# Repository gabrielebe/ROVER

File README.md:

# ROVER
Rover delevoped for the secondary school exam

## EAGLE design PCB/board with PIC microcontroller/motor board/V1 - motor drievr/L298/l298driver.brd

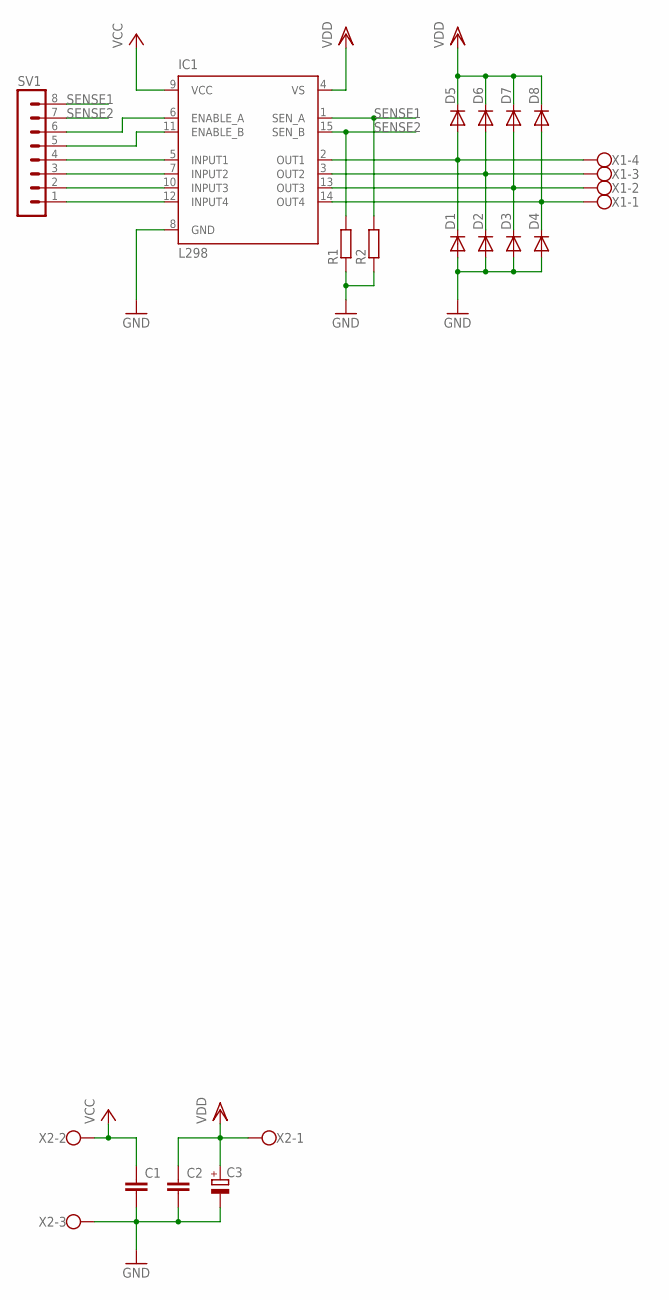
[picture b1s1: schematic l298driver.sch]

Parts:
C1, C2: C-EU050-024X044; C050-024X044
C3: CPOL-EUE3.5-10; E3,5-10
D1, D2, D3, D4, D5, D6, D7, D8: BA157; P1-10
IC1: L298; MULTIWATT-15
R1, R2: R-EU_RDH/15; RDH/15
SV1: MA08-1
X1: W237-4
X2: W237-103

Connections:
GND: C1.2, C2.2, C3.-, D1.A, D2.A, D3.A, D4.A, IC1.8 (GND), R1.1, R2.1, X2.3
unnamed: D1.C, D5.A, IC1.2 (OUT1), X1.4
unnamed: D2.C, D6.A, IC1.3 (OUT2), X1.3
unnamed: D3.C, D7.A, IC1.13 (OUT3), X1.2
unnamed: D4.C, D8.A, IC1.14 (OUT4), X1.1
unnamed: IC1.12 (INPUT4), SV1.1
unnamed: IC1.10 (INPUT3), SV1.2
unnamed: IC1.7 (INPUT2), SV1.3
unnamed: IC1.5 (INPUT1), SV1.4
unnamed: IC1.11 (ENABLE_B), SV1.5
unnamed: IC1.6 (ENABLE_A), SV1.6
SENSE1: IC1.1 (SEN_A), R2.2, SV1.8
SENSE2: IC1.15 (SEN_B), R1.2, SV1.7
VCC: C1.1, IC1.9 (VCC), X2.2
VDD: C2.1, C3.+, D5.C, D6.C, D7.C, D8.C, IC1.4 (VS), X2.1

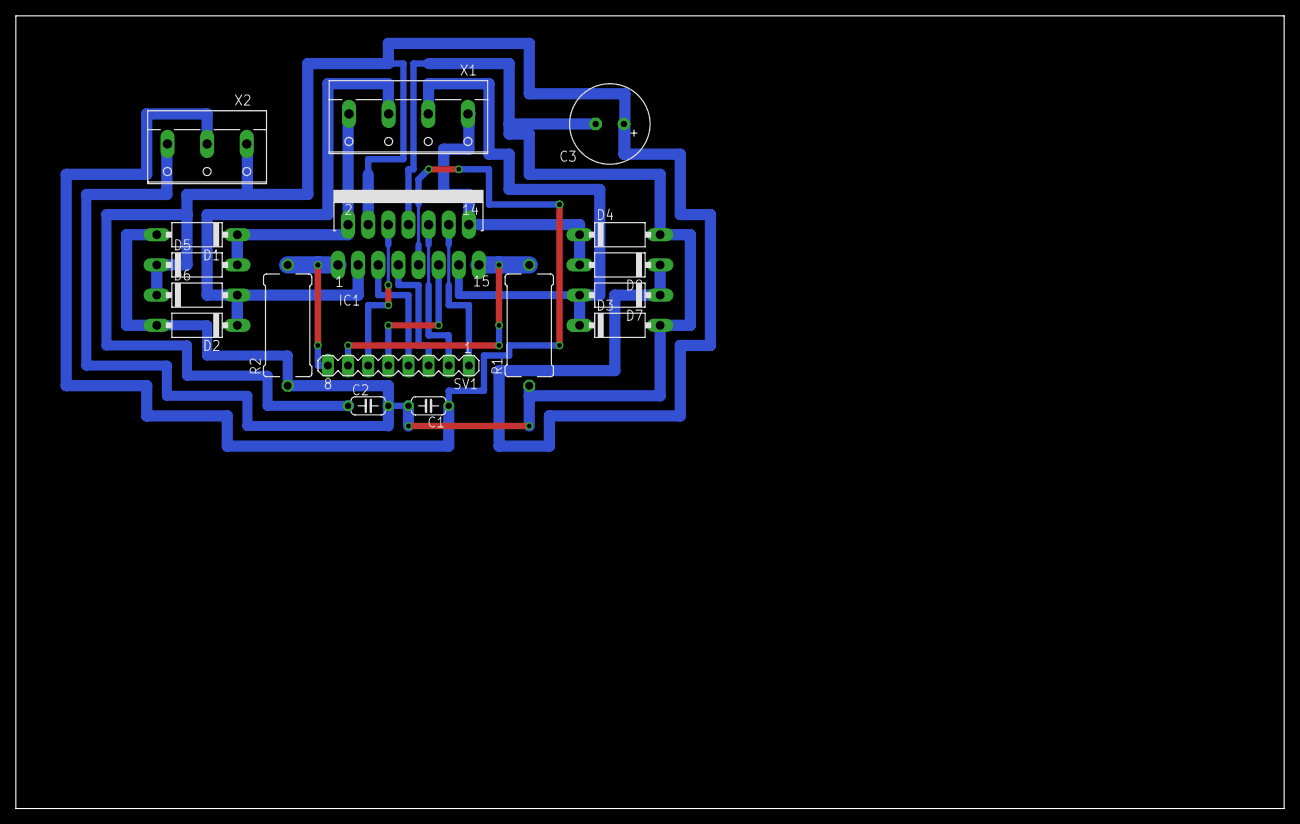
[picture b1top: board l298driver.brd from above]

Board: 2 copper layers, 160.0 x 100.0 mm, 17 parts (0 on the bottom side), 15 nets.

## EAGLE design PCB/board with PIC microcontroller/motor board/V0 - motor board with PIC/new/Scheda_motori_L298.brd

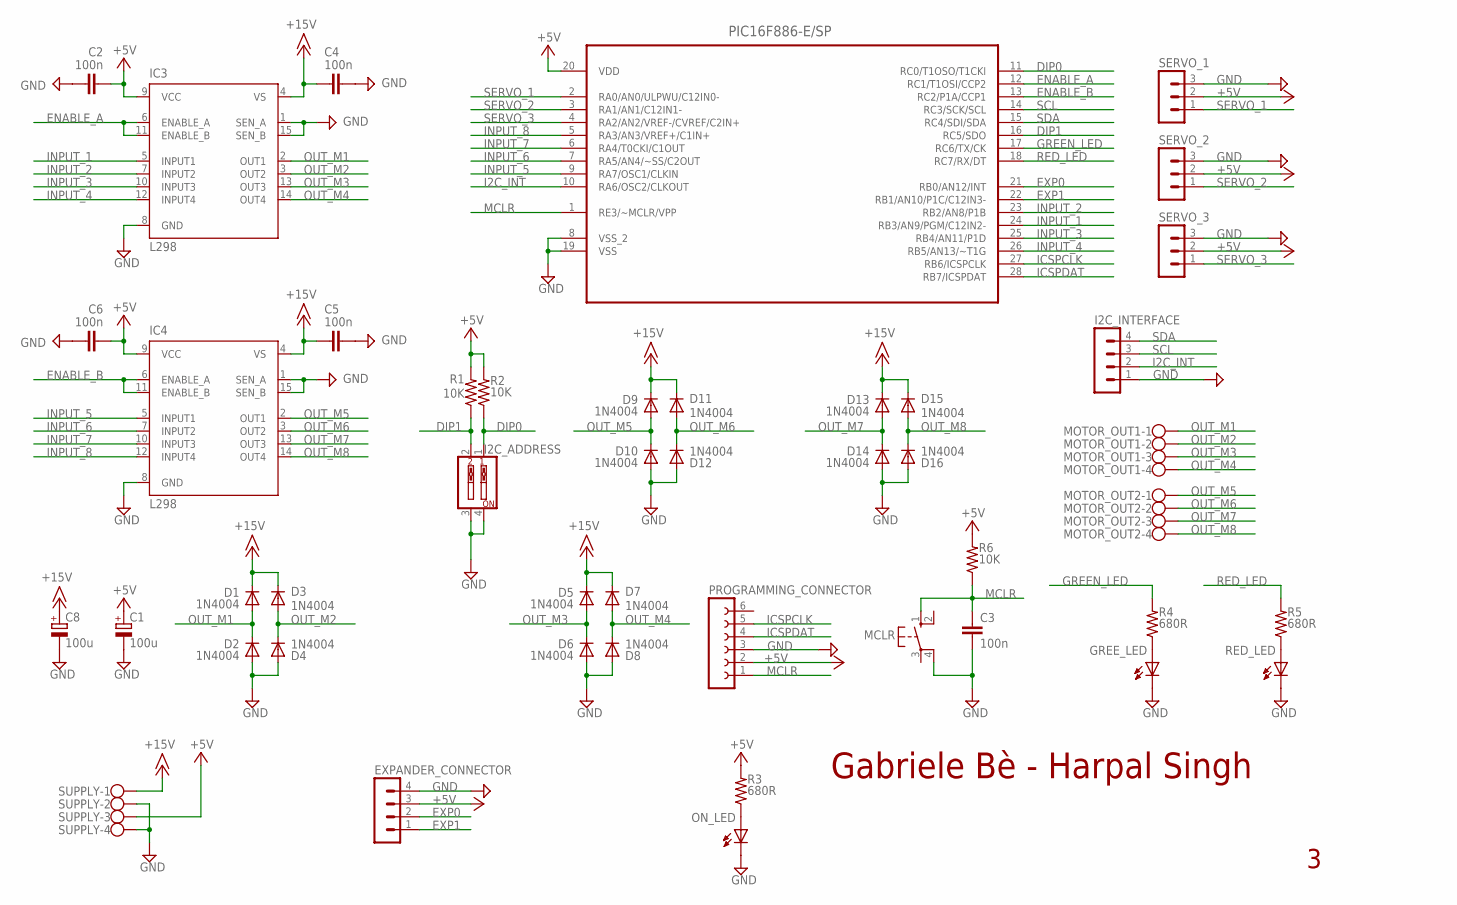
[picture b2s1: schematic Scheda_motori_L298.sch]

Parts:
C1, C8: 100u; E2,5-7
C2, C3, C4, C5, C6: 100n; C050-024X044
D1, D2, D3, D4, D5, D6, D7, D8, D9, D10, D11, D12, D13, D14, D15, D16: 1N4004; DO41-10
EXPANDER_CONNECTOR: MA04-1
GREE_LED: HLMP6
I2C_ADDRESS: SW_DIP-2; EDG-02
I2C_INTERFACE: MA04-1
IC3, IC4: L298; MULTIWATT-15
MCLR: 10-XX; B3F-10XX
MOTOR_OUT1, MOTOR_OUT2: W237-4
ON_LED: HLMP6
PROGRAMMING_CONNECTOR: FE06-1; FE06
R1, R2, R6: 10K; 0207/10
R3, R4, R5: 680R; 0207/10
RED_LED: HLMP6
SERVO_1, SERVO_2, SERVO_3: MA03-1
SUPPLY: W237-4
U$1: PIC16F886-E/SP; DIP254P762X508-28

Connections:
+5V: C1.+, C2.2, C6.2, EXPANDER_CONNECTOR.3, IC3.9 (VCC), IC4.9 (VCC), PROGRAMMING_CONNECTOR.2, R1.2, R2.2, R3.2, R6.2, SERVO_1.2, SERVO_2.2, SERVO_3.2, SUPPLY.3, U$1.20 (VDD)
+15V: C4.1, C5.1, C8.+, D1.C, D3.C, D5.C, D7.C, D9.C, D11.C, D13.C, D15.C, IC3.4 (VS), IC4.4 (VS), SUPPLY.1
DIP0: I2C_ADDRESS.1, R2.1, U$1.11 (RC0/T1OSO/T1CKI)
DIP1: I2C_ADDRESS.2, R1.1, U$1.16 (RC5/SDO)
ENABLE_A: IC3.6 (ENABLE_A), IC3.11 (ENABLE_B), U$1.12 (RC1/T1OSI/CCP2)
ENABLE_B: IC4.6 (ENABLE_A), IC4.11 (ENABLE_B), U$1.13 (RC2/P1A/CCP1)
EXP0: EXPANDER_CONNECTOR.2, U$1.21 (RB0/AN12/INT)
EXP1: EXPANDER_CONNECTOR.1, U$1.22 (RB1/AN10/P1C/C12IN3-)
GND: C1.-, C2.1, C3.2, C4.2, C5.2, C6.1, C8.-, D2.A, D4.A, D6.A, D8.A, D10.A, D12.A, D14.A, D16.A, EXPANDER_CONNECTOR.4, GREE_LED.K, I2C_ADDRESS.3, I2C_ADDRESS.4, I2C_INTERFACE.1, IC3.1 (SEN_A), IC3.8 (GND), IC3.15 (SEN_B), IC4.1 (SEN_A), IC4.8 (GND), IC4.15 (SEN_B), MCLR.4 (P1), ON_LED.K, PROGRAMMING_CONNECTOR.3, RED_LED.K, SERVO_1.3, SERVO_2.3, SERVO_3.3, SUPPLY.2, SUPPLY.4, U$1.8 (VSS_2), U$1.19 (VSS)
GREEN_LED: R4.2, U$1.17 (RC6/TX/CK)
I2C_INT: I2C_INTERFACE.2, U$1.10 (RA6/OSC2/CLKOUT)
ICSPCLK: PROGRAMMING_CONNECTOR.5, U$1.27 (RB6/ICSPCLK)
ICSPDAT: PROGRAMMING_CONNECTOR.4, U$1.28 (RB7/ICSPDAT)
INPUT_1: IC3.5 (INPUT1), U$1.24 (RB3/AN9/PGM/C12IN2-)
INPUT_2: IC3.7 (INPUT2), U$1.23 (RB2/AN8/P1B)
INPUT_3: IC3.10 (INPUT3), U$1.25 (RB4/AN11/P1D)
INPUT_4: IC3.12 (INPUT4), U$1.26 (RB5/AN13/~T1G)
INPUT_5: IC4.5 (INPUT1), U$1.9 (RA7/OSC1/CLKIN)
INPUT_6: IC4.7 (INPUT2), U$1.7 (RA5/AN4/~SS/C2OUT)
INPUT_7: IC4.10 (INPUT3), U$1.6 (RA4/T0CKI/C1OUT)
INPUT_8: IC4.12 (INPUT4), U$1.5 (RA3/AN3/VREF+/C1IN+)
MCLR: C3.1, MCLR.1 (S), PROGRAMMING_CONNECTOR.1, R6.1, U$1.1 (RE3/~MCLR/VPP)
unnamed: ON_LED.A, R3.1
unnamed: GREE_LED.A, R4.1
unnamed: R5.1, RED_LED.A
OUT_M1: D1.A, D2.C, IC3.2 (OUT1), MOTOR_OUT1.1
OUT_M2: D3.A, D4.C, IC3.3 (OUT2), MOTOR_OUT1.2
OUT_M3: D5.A, D6.C, IC3.13 (OUT3), MOTOR_OUT1.3
OUT_M4: D7.A, D8.C, IC3.14 (OUT4), MOTOR_OUT1.4
OUT_M5: D9.A, D10.C, IC4.2 (OUT1), MOTOR_OUT2.1
OUT_M6: D11.A, D12.C, IC4.3 (OUT2), MOTOR_OUT2.2
OUT_M7: D13.A, D14.C, IC4.13 (OUT3), MOTOR_OUT2.3
OUT_M8: D15.A, D16.C, IC4.14 (OUT4), MOTOR_OUT2.4
RED_LED: R5.2, U$1.18 (RC7/RX/DT)
SCL: I2C_INTERFACE.3, U$1.14 (RC3/SCK/SCL)
SDA: I2C_INTERFACE.4, U$1.15 (RC4/SDI/SDA)
SERVO_1: SERVO_1.1, U$1.2 (RA0/AN0/ULPWU/C12IN0-)
SERVO_2: SERVO_2.1, U$1.3 (RA1/AN1/C12IN1-)
SERVO_3: SERVO_3.1, U$1.4 (RA2/AN2/VREF-/CVREF/C2IN+)

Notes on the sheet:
Gabriele Bè - Harpal Singh

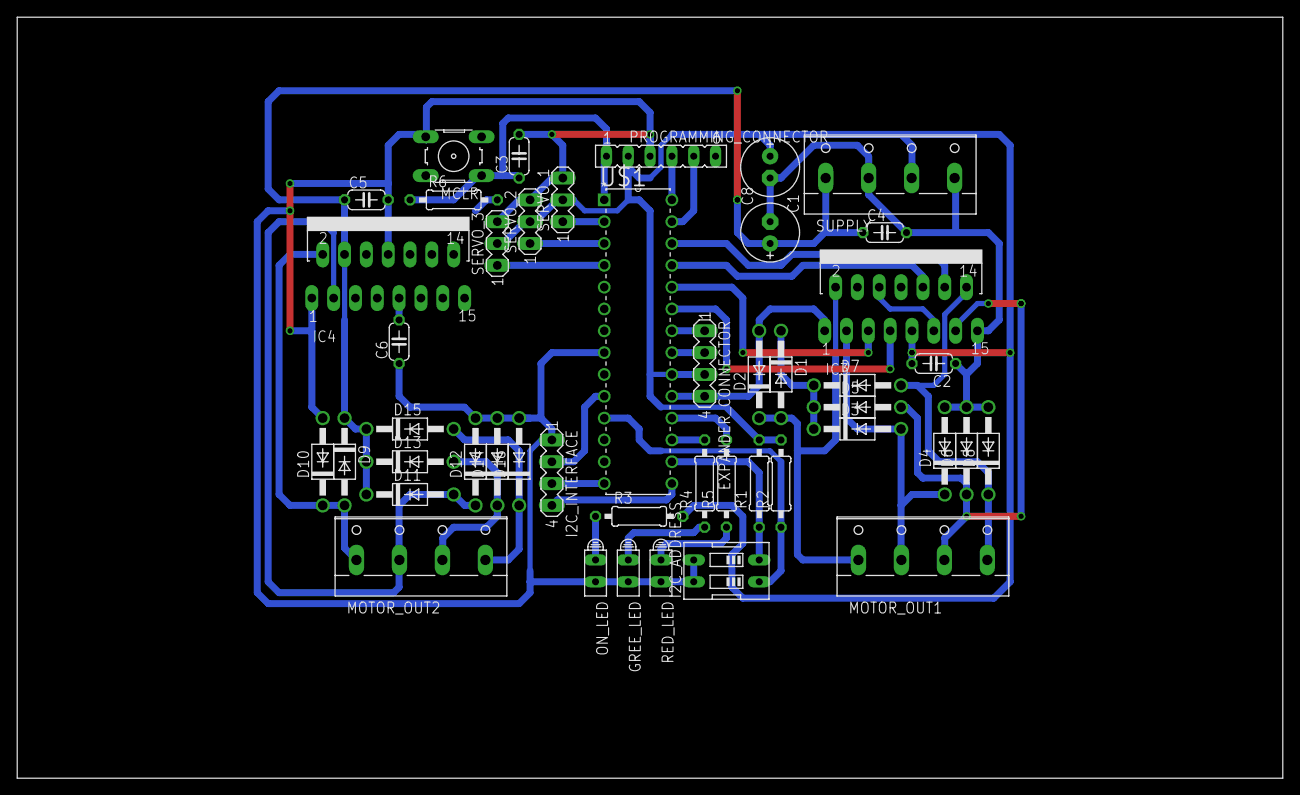
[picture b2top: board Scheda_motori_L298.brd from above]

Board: 2 copper layers, 147.3 x 88.6 mm, 46 parts (0 on the bottom side), 39 nets.

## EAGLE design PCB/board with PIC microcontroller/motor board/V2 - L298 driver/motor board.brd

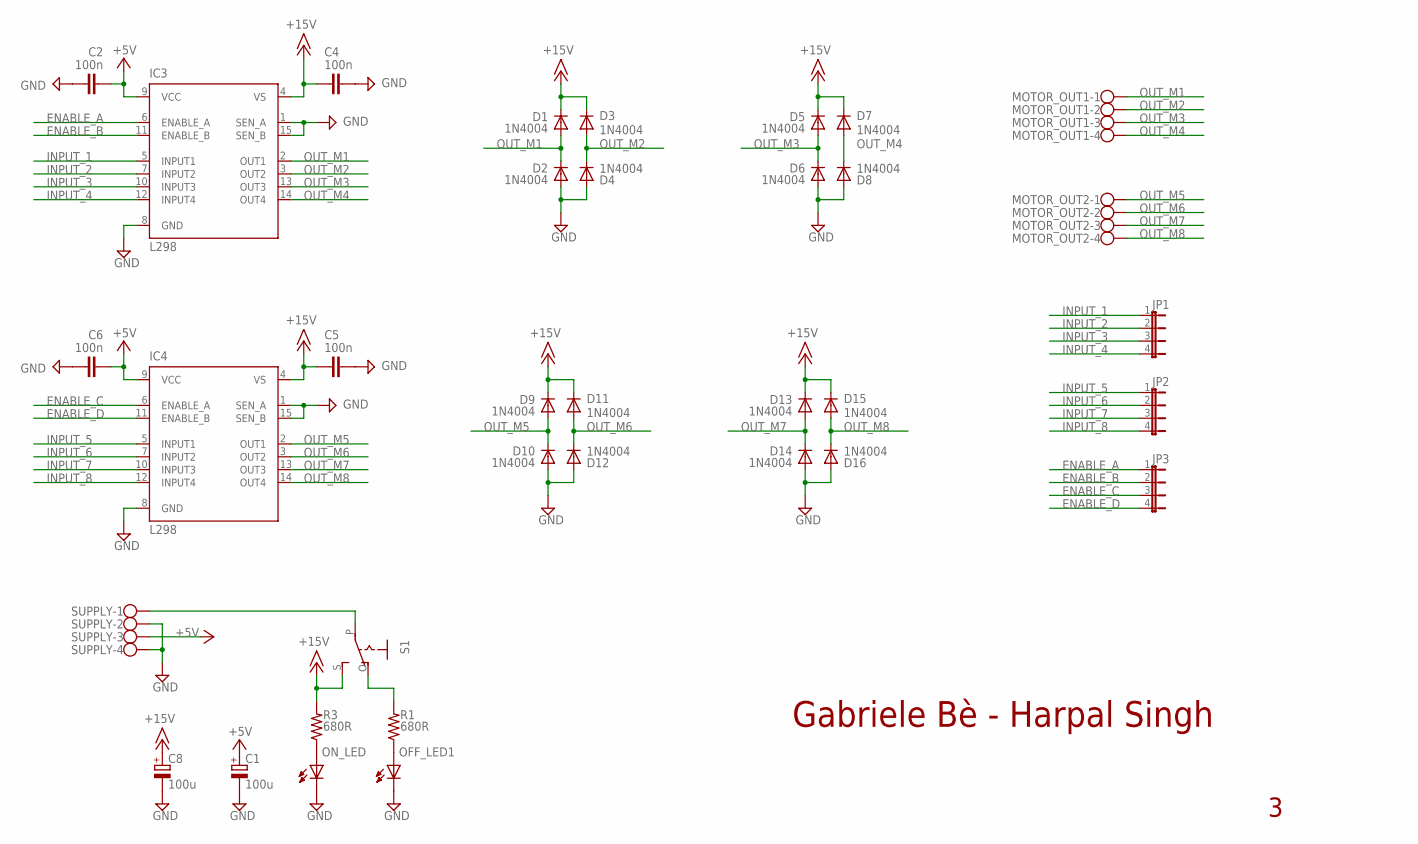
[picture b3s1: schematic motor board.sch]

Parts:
C1, C8: 100u; E2,5-7
C2, C4, C5, C6: 100n; C050-024X044
D1, D2, D3, D4, D5, D6, D7, D8, D9, D10, D11, D12, D13, D14, D15, D16: 1N4004; DO41-10
IC3, IC4: L298; MULTIWATT-15
JP1, JP2, JP3: JP4E; JP4
MOTOR_OUT1, MOTOR_OUT2: W237-4
OFF_LED1: HLMP6
ON_LED: HLMP6
R1, R3: 680R; 0207/10
S1: EG1218S; EG1218
SUPPLY: W237-4

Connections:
+5V: C1.+, C2.2, C6.2, IC3.9 (VCC), IC4.9 (VCC), SUPPLY.3
+15V: C4.1, C5.1, C8.+, D1.C, D3.C, D5.C, D7.C, D9.C, D11.C, D13.C, D15.C, IC3.4 (VS), IC4.4 (VS), R3.2, S1.S
ENABLE_A: IC3.6 (ENABLE_A), JP3.1
ENABLE_B: IC3.11 (ENABLE_B), JP3.2
ENABLE_C: IC4.6 (ENABLE_A), JP3.3
ENABLE_D: IC4.11 (ENABLE_B), JP3.4
GND: C1.-, C2.1, C4.2, C5.2, C6.1, C8.-, D2.A, D4.A, D6.A, D8.A, D10.A, D12.A, D14.A, D16.A, IC3.1 (SEN_A), IC3.8 (GND), IC3.15 (SEN_B), IC4.1 (SEN_A), IC4.8 (GND), IC4.15 (SEN_B), OFF_LED1.K, ON_LED.K, SUPPLY.2, SUPPLY.4
INPUT_1: IC3.5 (INPUT1), JP1.1
INPUT_2: IC3.7 (INPUT2), JP1.2
INPUT_3: IC3.10 (INPUT3), JP1.3
INPUT_4: IC3.12 (INPUT4), JP1.4
INPUT_5: IC4.5 (INPUT1), JP2.1
INPUT_6: IC4.7 (INPUT2), JP2.2
INPUT_7: IC4.10 (INPUT3), JP2.3
INPUT_8: IC4.12 (INPUT4), JP2.4
unnamed: OFF_LED1.A, R1.1
unnamed: ON_LED.A, R3.1
unnamed: S1.P, SUPPLY.1
unnamed: R1.2, S1.O
OUT_M1: D1.A, D2.C, IC3.2 (OUT1), MOTOR_OUT1.1
OUT_M2: D3.A, D4.C, IC3.3 (OUT2), MOTOR_OUT1.2
OUT_M3: D5.A, D6.C, IC3.13 (OUT3), MOTOR_OUT1.3
OUT_M4: D7.A, D8.C, IC3.14 (OUT4), MOTOR_OUT1.4
OUT_M5: D9.A, D10.C, IC4.2 (OUT1), MOTOR_OUT2.1
OUT_M6: D11.A, D12.C, IC4.3 (OUT2), MOTOR_OUT2.2
OUT_M7: D13.A, D14.C, IC4.13 (OUT3), MOTOR_OUT2.3
OUT_M8: D15.A, D16.C, IC4.14 (OUT4), MOTOR_OUT2.4

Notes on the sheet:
Gabriele Bè - Harpal Singh

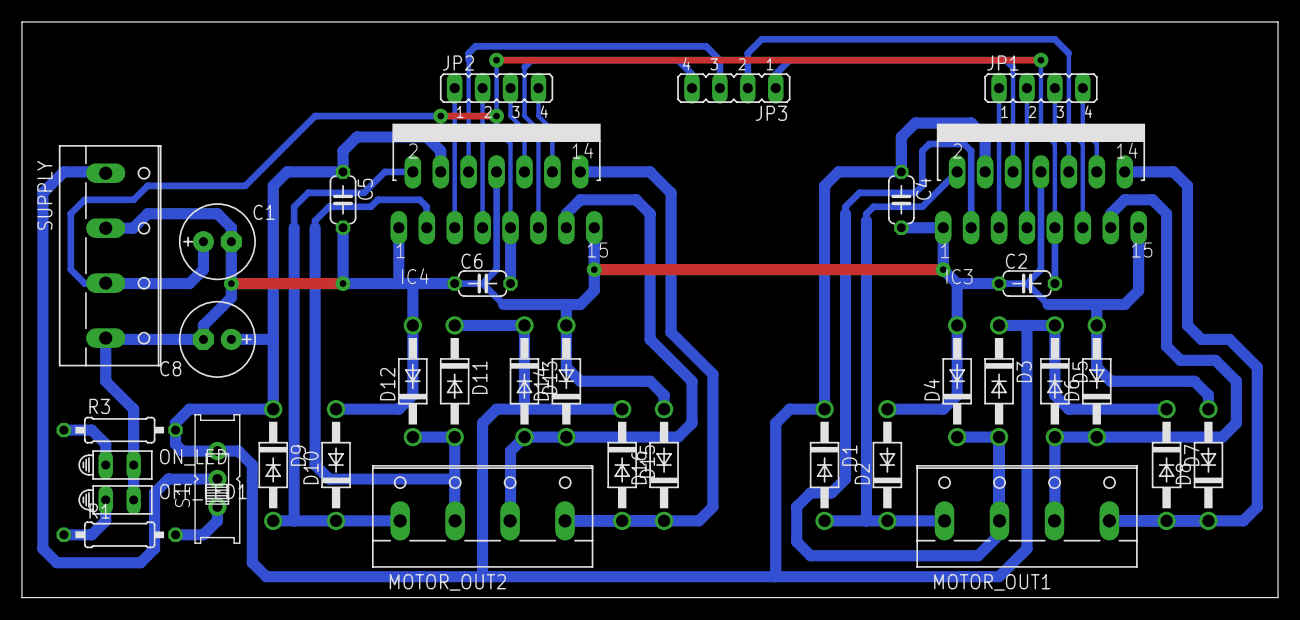
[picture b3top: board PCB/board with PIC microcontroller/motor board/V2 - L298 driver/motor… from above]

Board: 2 copper layers, 114.3 x 52.4 mm, 35 parts (0 on the bottom side), 27 nets.

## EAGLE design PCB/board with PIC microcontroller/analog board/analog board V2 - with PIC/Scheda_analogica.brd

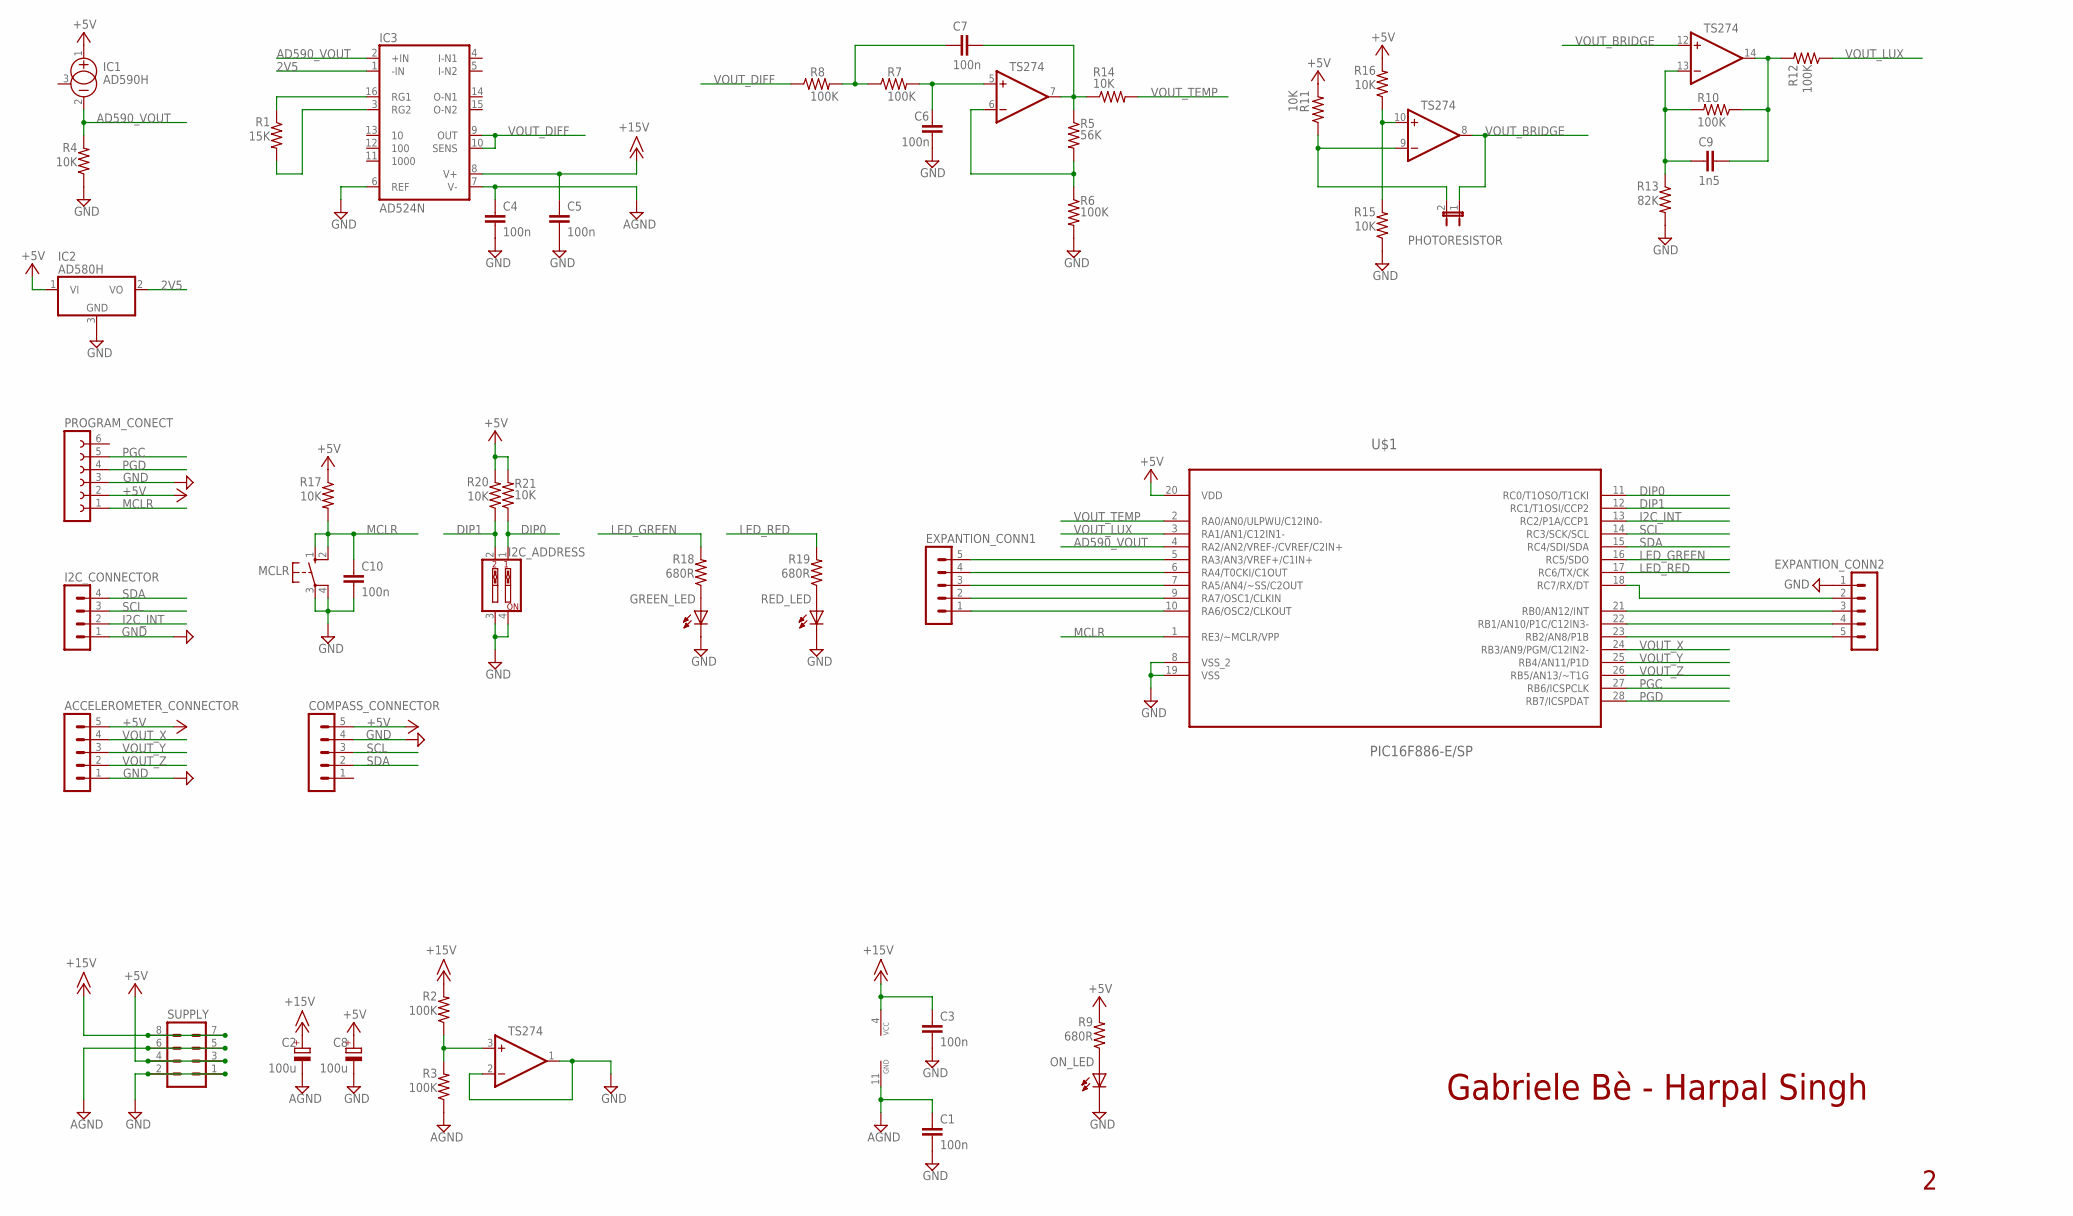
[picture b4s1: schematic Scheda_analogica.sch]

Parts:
ACCELEROMETER_CONNECTOR: MA05-1
C1, C3, C4, C5, C6, C7, C10: 100n; C050-024X044
C2, C8: 100u; E2,5-7
C9: 1n5; C050-024X044
COMPASS_CONNECTOR: MA05-1
EXPANTION_CONN1, EXPANTION_CONN2: MA05-1
GREEN_LED: HLMP6
I2C_ADDRESS: SW_DIP-2; EDG-02
I2C_CONNECTOR: MA04-1
IC1: AD590H; TO18
IC2: AD580H; TO39
IC3: AD524N; DIL16
IC4: TS274; DIL14
MCLR: 10-XX; B3F-10XX
ON_LED: HLMP6
PHOTORESISTOR: JP1E; JP1
PROGRAM_CONECT: FE06-1; FE06
R1: 15K; 0207/10
R2, R3, R6, R7, R8, R10, R12: 100K; 0207/10
R4, R11, R14, R15, R16, R17, R20, R21: 10K; 0207/10
R5: 56K; 0207/10
R9, R18, R19: 680R; 0207/10
R13: 82K; 0207/10
RED_LED: HLMP6
SUPPLY: MA04-2
U$1: PIC16F886-E/SP; DIP254P762X508-28

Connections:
2V5: IC2.2 (VO), IC3.1 (-IN)
+5V: ACCELEROMETER_CONNECTOR.5, C8.+, COMPASS_CONNECTOR.5, IC1.1 (+), IC2.1 (VI), PROGRAM_CONECT.2, R9.2, R11.2, R16.2, R17.1, R20.2, R21.2, SUPPLY.3, SUPPLY.4, U$1.20 (VDD)
+15V: C2.+, C3.1, C5.1, IC3.8 (V+), IC4.4 (VCC), R2.2, SUPPLY.7, SUPPLY.8
AD590_VOUT: IC1.2 (-), IC3.2 (+IN), R4.2, U$1.4 (RA2/AN2/VREF-/CVREF/C2IN+)
AGND: C1.1, C2.-, C4.1, IC3.7 (V-), IC4.11 (GND), R3.1, SUPPLY.5, SUPPLY.6
DIP0: I2C_ADDRESS.1, R21.1, U$1.11 (RC0/T1OSO/T1CKI)
DIP1: I2C_ADDRESS.2, R20.1, U$1.12 (RC1/T1OSI/CCP2)
GND: ACCELEROMETER_CONNECTOR.1, C1.2, C3.2, C4.2, C5.2, C6.2, C8.-, C10.2, COMPASS_CONNECTOR.4, EXPANTION_CONN2.1, GREEN_LED.K, I2C_ADDRESS.3, I2C_ADDRESS.4, I2C_CONNECTOR.1, IC2.3 (GND), IC3.6 (REF), IC4.1 (OUT), IC4.2 (-IN), MCLR.3, MCLR.4 (P1), ON_LED.K, PROGRAM_CONECT.3, R4.1, R6.2, R13.2, R15.1, RED_LED.K, SUPPLY.1, SUPPLY.2, U$1.8 (VSS_2), U$1.19 (VSS)
I2C_INT: I2C_CONNECTOR.2, U$1.13 (RC2/P1A/CCP1)
LED_GREEN: R18.2, U$1.16 (RC5/SDO)
LED_RED: R19.2, U$1.17 (RC6/TX/CK)
MCLR: C10.1, MCLR.1 (S), MCLR.2 (S1), PROGRAM_CONECT.1, R17.2, U$1.1 (RE3/~MCLR/VPP)
unnamed: IC3.16 (RG1), R1.1
unnamed: IC3.3 (RG2), R1.2
unnamed: IC4.6 (-IN), R5.2, R6.1
unnamed: ON_LED.A, R9.1
unnamed: IC4.3 (+IN), R2.1, R3.2
unnamed: C6.1, IC4.5 (+IN), R7.2
unnamed: C7.1, R7.1, R8.2
unnamed: C7.2, IC4.7 (OUT), R5.1, R14.1
unnamed: IC4.9 (-IN), PHOTORESISTOR.2, R11.1
unnamed: GREEN_LED.A, R18.1
unnamed: IC4.10 (+IN), R15.2, R16.1
unnamed: C9.1, IC4.13 (-IN), R10.2, R13.1
unnamed: C9.2, IC4.14 (OUT), R10.1, R12.2
unnamed: R19.1, RED_LED.A
unnamed: EXPANTION_CONN1.1, U$1.10 (RA6/OSC2/CLKOUT)
unnamed: EXPANTION_CONN1.2, U$1.9 (RA7/OSC1/CLKIN)
unnamed: EXPANTION_CONN1.3, U$1.7 (RA5/AN4/~SS/C2OUT)
unnamed: EXPANTION_CONN1.4, U$1.6 (RA4/T0CKI/C1OUT)
unnamed: EXPANTION_CONN1.5, U$1.5 (RA3/AN3/VREF+/C1IN+)
unnamed: EXPANTION_CONN2.2, U$1.18 (RC7/RX/DT)
unnamed: EXPANTION_CONN2.3, U$1.21 (RB0/AN12/INT)
unnamed: EXPANTION_CONN2.4, U$1.22 (RB1/AN10/P1C/C12IN3-)
unnamed: EXPANTION_CONN2.5, U$1.23 (RB2/AN8/P1B)
PGC: PROGRAM_CONECT.5, U$1.27 (RB6/ICSPCLK)
PGD: PROGRAM_CONECT.4, U$1.28 (RB7/ICSPDAT)
SCL: COMPASS_CONNECTOR.3, I2C_CONNECTOR.3, U$1.14 (RC3/SCK/SCL)
SDA: COMPASS_CONNECTOR.2, I2C_CONNECTOR.4, U$1.15 (RC4/SDI/SDA)
VOUT_BRIDGE: IC4.8 (OUT), IC4.12 (+IN), PHOTORESISTOR.1
VOUT_DIFF: IC3.9 (OUT), IC3.10 (SENS), R8.1
VOUT_LUX: R12.1, U$1.3 (RA1/AN1/C12IN1-)
VOUT_TEMP: R14.2, U$1.2 (RA0/AN0/ULPWU/C12IN0-)
VOUT_X: ACCELEROMETER_CONNECTOR.4, U$1.24 (RB3/AN9/PGM/C12IN2-)
VOUT_Y: ACCELEROMETER_CONNECTOR.3, U$1.25 (RB4/AN11/P1D)
VOUT_Z: ACCELEROMETER_CONNECTOR.2, U$1.26 (RB5/AN13/~T1G)

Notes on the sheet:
Gabriele Bè - Harpal Singh

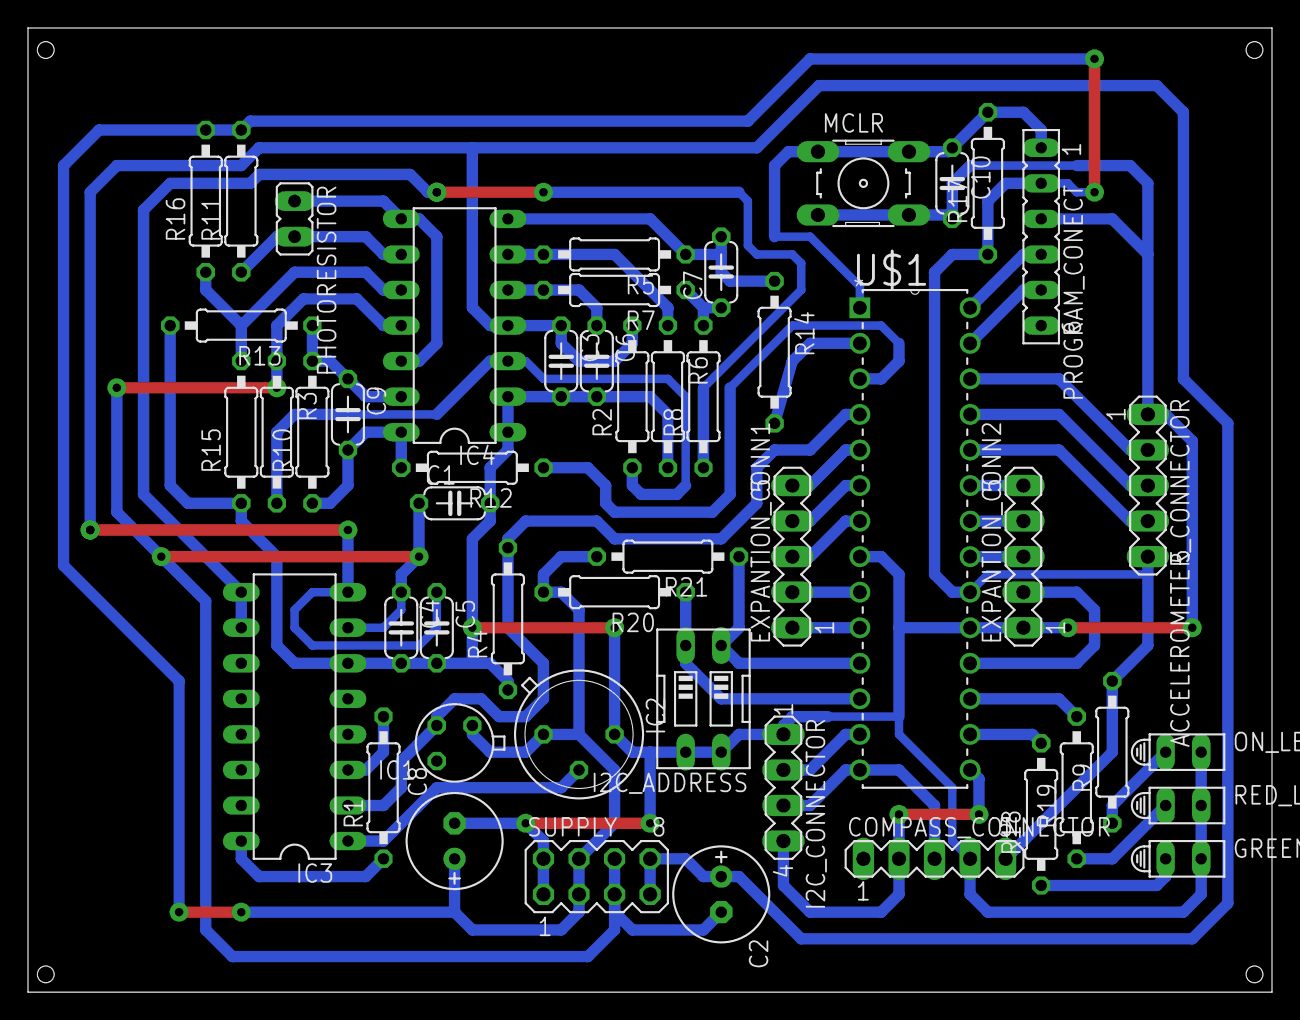
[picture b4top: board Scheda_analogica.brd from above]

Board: 2 copper layers, 88.9 x 68.9 mm, 49 parts (0 on the bottom side), 46 nets.

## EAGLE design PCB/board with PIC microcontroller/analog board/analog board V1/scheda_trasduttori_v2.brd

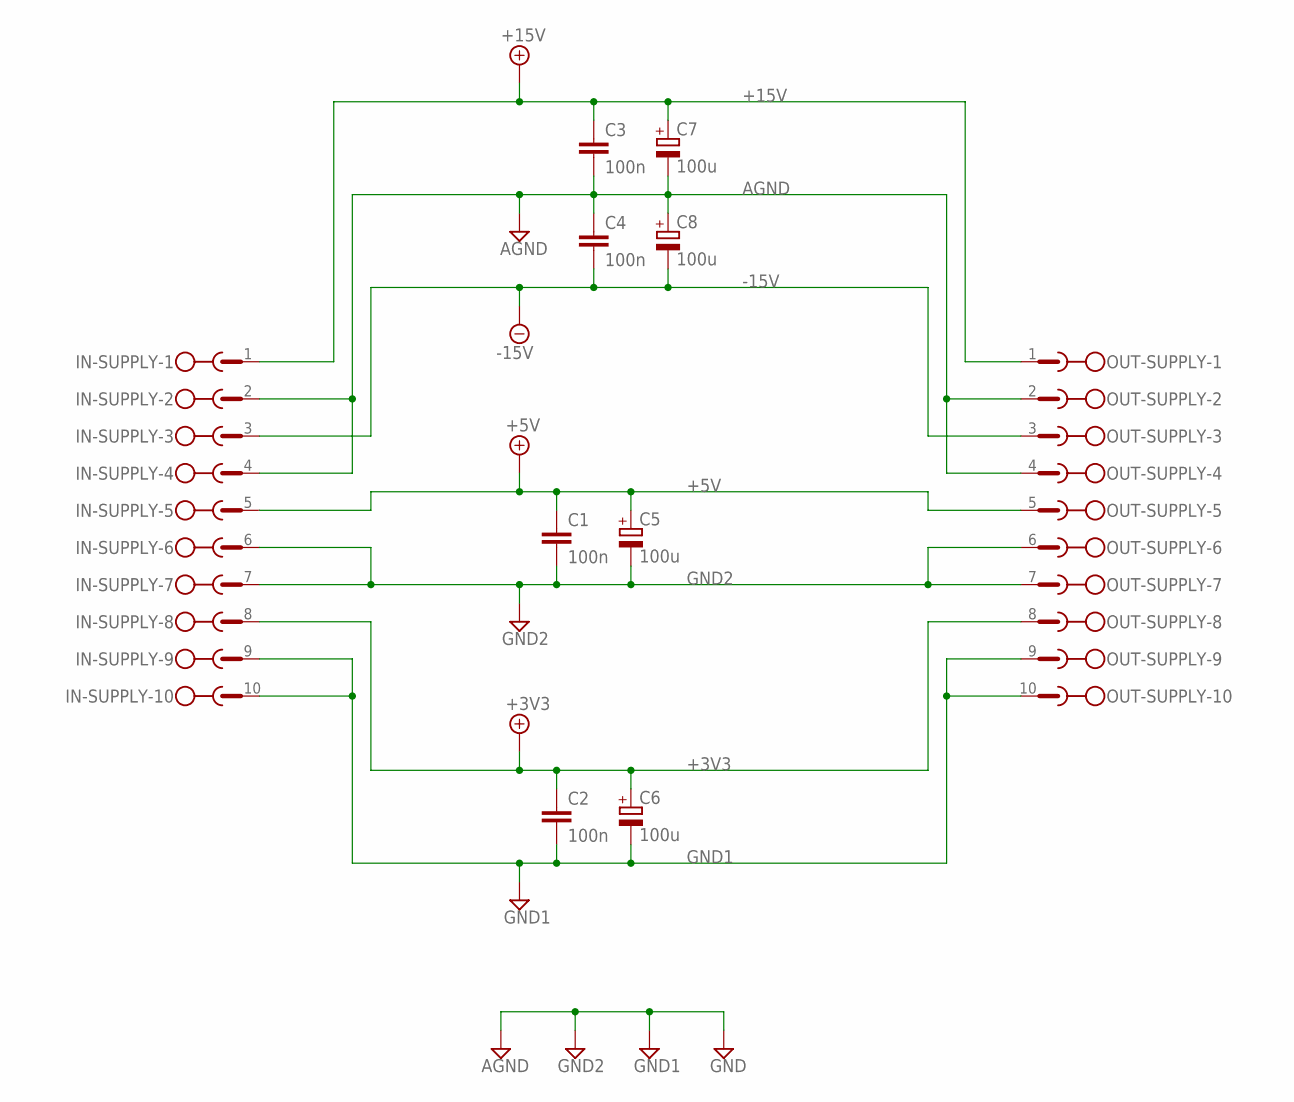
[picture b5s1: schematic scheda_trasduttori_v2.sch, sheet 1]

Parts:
C1, C2, C3, C4: 100n; C2.5-3
C5, C6, C7, C8: 100u; E2,5-7
IN-SUPPLY: MSTBA10
OUT-SUPPLY: MSTBA10

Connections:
+3V3: C2.1, C6.+, IN-SUPPLY.8, OUT-SUPPLY.8
+5V: C1.1, C5.+, IN-SUPPLY.5, OUT-SUPPLY.5; also elsewhere on the board
+15V: C3.1, C7.+, IN-SUPPLY.1, OUT-SUPPLY.1; also elsewhere on the board
-15V: C4.2, C8.-, IN-SUPPLY.3, OUT-SUPPLY.3; also elsewhere on the board
AGND: C3.2, C4.1, C7.-, C8.+, IN-SUPPLY.2, IN-SUPPLY.4, OUT-SUPPLY.2, OUT-SUPPLY.4; also elsewhere on the board
GND1: C2.2, C6.-, IN-SUPPLY.9, IN-SUPPLY.10, OUT-SUPPLY.9, OUT-SUPPLY.10; also elsewhere on the board
GND2: C1.2, C5.-, IN-SUPPLY.6, IN-SUPPLY.7, OUT-SUPPLY.6, OUT-SUPPLY.7; also elsewhere on the board

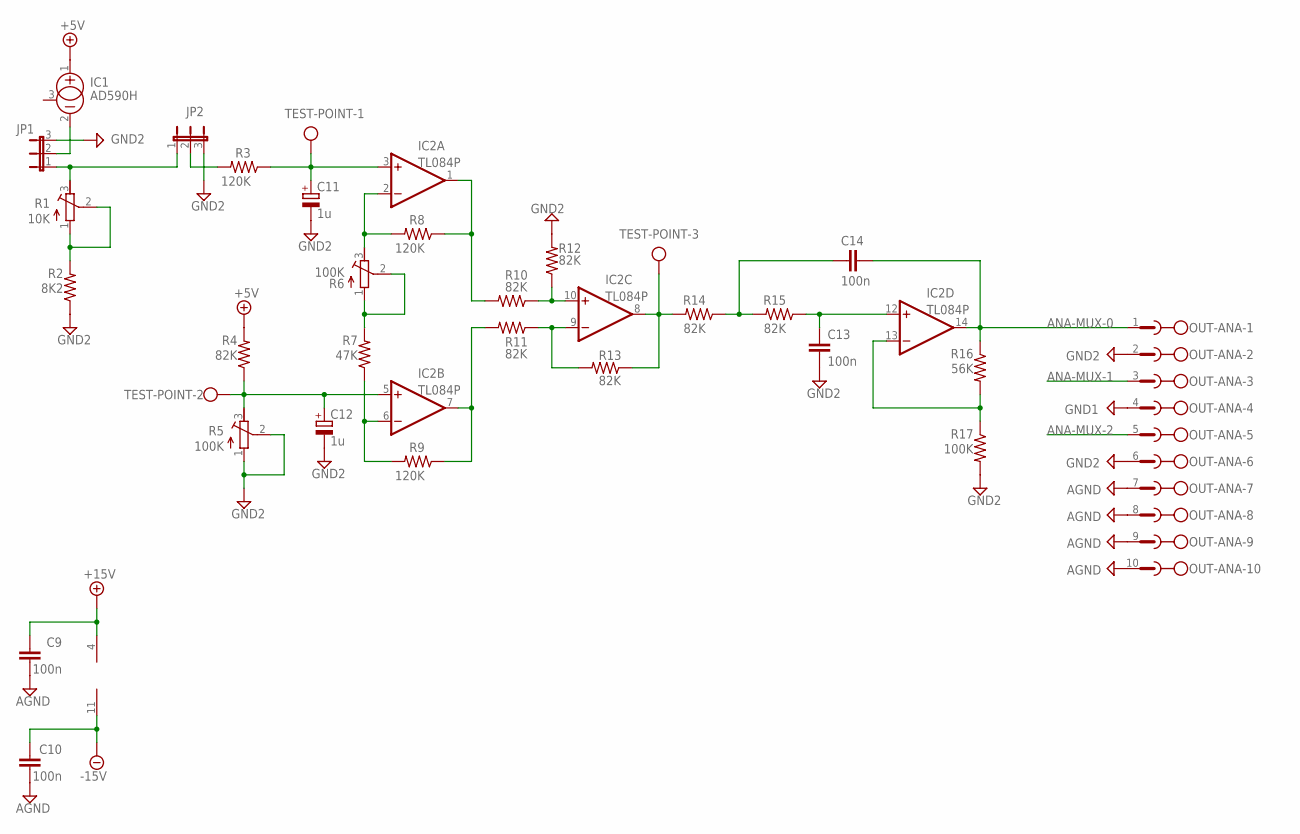
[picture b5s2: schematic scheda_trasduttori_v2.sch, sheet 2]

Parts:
C9, C10, C13, C14: 100n; C025-024X044
C11, C12: 1u; E5-8,5
IC1: AD590H; TO18
IC2: TL084P; DIL14
JP1, JP2: JP2E; JP2
OUT-ANA: MSTBA10
R1: 10K; RTRIM64W
R2: 8K2; 0204/7
R3, R8, R9: 120K; 0204/7
R4, R10, R11, R12, R13, R14, R15: 82K; 0204/7
R5, R6: 100K; RTRIM64W
R7: 47K; 0204/7
R16: 56K; 0204/7
R17: 100K; 0204/7
TEST-POINT: W237-103

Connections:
+5V: IC1.1 (+), R4.2; also elsewhere on the board
+15V: C9.2, IC2.4 (V+); also elsewhere on the board
-15V: C10.2, IC2.11 (V-); also elsewhere on the board
AGND: C9.1, C10.1, OUT-ANA.7, OUT-ANA.8, OUT-ANA.9, OUT-ANA.10; also elsewhere on the board
ANA-MUX-0: C14.2, IC2.14 (OUT), OUT-ANA.1, R16.1
ANA-MUX-1: OUT-ANA.3; also elsewhere on the board
ANA-MUX-2: OUT-ANA.5; also elsewhere on the board
GND1: OUT-ANA.4; also elsewhere on the board
GND2: C11.-, C12.-, C13.1, JP1.3, JP2.3, OUT-ANA.2, OUT-ANA.6, R2.1, R5.1 (E), R5.2 (S), R12.2, R17.2; also elsewhere on the board
unnamed: R1.1 (E), R1.2 (S), R2.2
unnamed: IC1.2 (-), JP1.2
unnamed: R6.1 (E), R6.2 (S), R7.2
unnamed: C11.+, IC2.3 (+IN), R3.1, TEST-POINT.1
unnamed: IC2.2 (-IN), R6.3 (A), R8.2
unnamed: IC2.1 (OUT), R8.1, R10.2
unnamed: JP2.2, R3.2
unnamed: JP1.1, JP2.1, R1.3 (A)
unnamed: C12.+, IC2.5 (+IN), R4.1, R5.3 (A), TEST-POINT.2
unnamed: IC2.6 (-IN), R7.1, R9.2
unnamed: IC2.7 (OUT), R9.1, R11.2
unnamed: IC2.10 (+IN), R10.1, R12.1
unnamed: IC2.9 (-IN), R11.1, R13.2
unnamed: IC2.8 (OUT), R13.1, R14.2, TEST-POINT.3
unnamed: C14.1, R14.1, R15.2
unnamed: C13.2, IC2.12 (+IN), R15.1
unnamed: IC2.13 (-IN), R16.2, R17.1

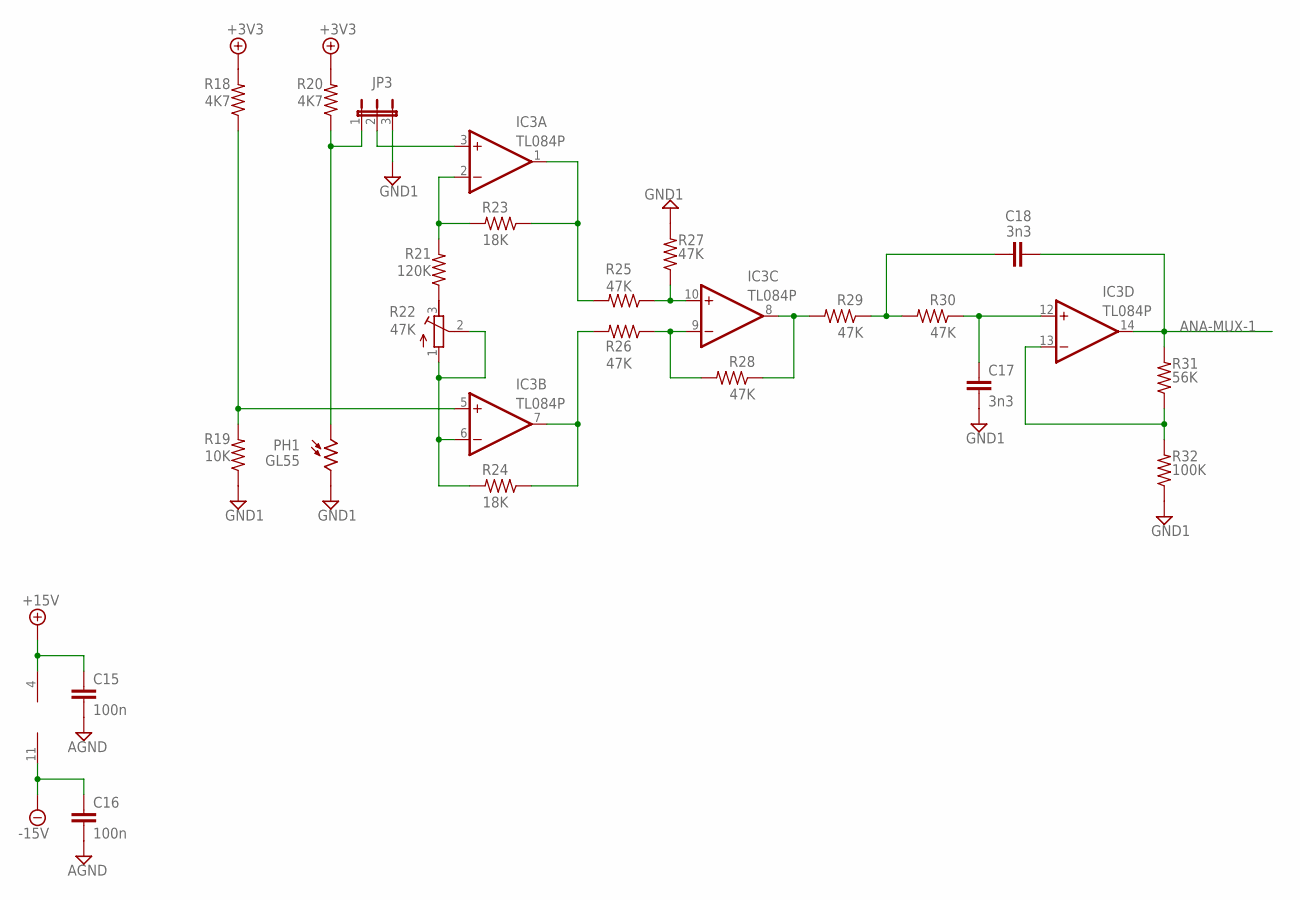
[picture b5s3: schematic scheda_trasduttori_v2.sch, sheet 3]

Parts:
C15, C16: 100n; C025-025X050
C17, C18: 3n3; C025-025X050
IC3: TL084P; DIL14
JP3: JP2E; JP2
PH1: GL55; T0-46-A10XX
R18, R20: 4K7; 0204/7
R19: 10K; 0204/7
R21: 120K; 0204/7
R22: 47K; RTRIM64W
R23, R24: 18K; 0204/7
R25, R26, R27, R28, R29, R30: 47K; 0204/7
R31: 56K; 0204/7
R32: 100K; 0204/7

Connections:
+4.1V: R18.2, R20.2
+15V: C15.1, IC3.4 (V+); also elsewhere on the board
-15V: C16.1, IC3.11 (V-); also elsewhere on the board
AGND: C15.2, C16.2; also elsewhere on the board
ANA-MUX-1: C18.2, IC3.14 (OUT), R31.2; also elsewhere on the board
GND1: C17.2, JP3.3, PH1.2, R19.1, R27.2, R32.1; also elsewhere on the board
unnamed: IC3.5 (+IN), R18.1, R19.2
unnamed: JP3.1, PH1.1, R20.1
unnamed: R21.1, R22.3 (A)
unnamed: IC3.6 (-IN), R22.1 (E), R22.2 (S), R24.2
unnamed: IC3.7 (OUT), R24.1, R26.2
unnamed: IC3.1 (OUT), R23.1, R25.2
unnamed: IC3.2 (-IN), R21.2, R23.2
unnamed: IC3.10 (+IN), R25.1, R27.1
unnamed: IC3.9 (-IN), R26.1, R28.2
unnamed: IC3.8 (OUT), R28.1, R29.2
unnamed: C17.1, IC3.12 (+IN), R30.1
unnamed: IC3.13 (-IN), R31.1, R32.2
unnamed: C18.1, R29.1, R30.2
unnamed: IC3.3 (+IN), JP3.2

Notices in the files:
parts and their libraries:
SparkFun-Passives: Licensing: Creative Commons ShareAlike 4.0 International - https://creativecommons.org/licenses/by-sa/4.0
